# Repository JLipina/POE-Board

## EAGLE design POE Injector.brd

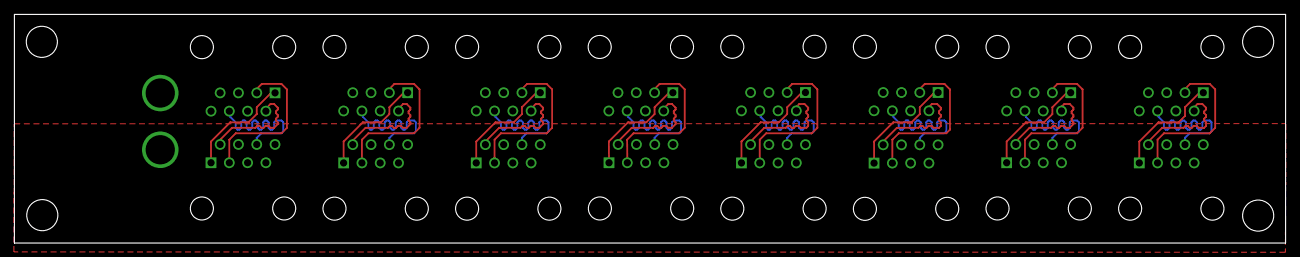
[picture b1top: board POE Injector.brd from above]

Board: 2 copper layers, 176.5 x 31.8 mm, 17 parts (0 on the bottom side), 34 nets.

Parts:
RJ45_ETH_1, RJ45_ETH_2, RJ45_ETH_3, RJ45_ETH_4, RJ45_ETH_5, RJ45_ETH_6, RJ45_ETH_7, RJ45_ETH_8, RJ45_POE_1, RJ45_POE_2, RJ45_POE_3, RJ45_POE_4, RJ45_POE_5, RJ45_POE_6, RJ45_POE_7, RJ45_POE_8: RJ45FCI-54602-908LF; FCI-54602-908LF
U$17: APP_2POS_CONFIG12V_HORIZ; APP45_12V_HORIZ_CONFIG

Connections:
+12V: RJ45_POE_1.4, RJ45_POE_1.5, RJ45_POE_2.4, RJ45_POE_2.5, RJ45_POE_3.4, RJ45_POE_3.5, RJ45_POE_4.4, RJ45_POE_4.5, RJ45_POE_5.4, RJ45_POE_5.5, RJ45_POE_6.4, RJ45_POE_6.5, RJ45_POE_7.4, RJ45_POE_7.5, RJ45_POE_8.4, RJ45_POE_8.5, U$17.12V
GND: RJ45_ETH_1.7, RJ45_ETH_1.8, RJ45_ETH_2.7, RJ45_ETH_2.8, RJ45_ETH_3.7, RJ45_ETH_3.8, RJ45_ETH_4.7, RJ45_ETH_4.8, RJ45_ETH_5.7, RJ45_ETH_5.8, RJ45_ETH_6.7, RJ45_ETH_6.8, RJ45_ETH_7.7, RJ45_ETH_7.8, RJ45_ETH_8.7, RJ45_ETH_8.8, RJ45_POE_1.7, RJ45_POE_1.8, RJ45_POE_2.7, RJ45_POE_2.8, RJ45_POE_3.7, RJ45_POE_3.8, RJ45_POE_4.7, RJ45_POE_4.8, RJ45_POE_5.7, RJ45_POE_5.8, RJ45_POE_6.7, RJ45_POE_6.8, RJ45_POE_7.7, RJ45_POE_7.8, RJ45_POE_8.7, RJ45_POE_8.8, U$17.GND
RX_N_1: RJ45_ETH_1.6, RJ45_POE_1.6
RX_N_2: RJ45_ETH_2.6, RJ45_POE_2.6
RX_N_3: RJ45_ETH_3.6, RJ45_POE_3.6
RX_N_4: RJ45_ETH_4.6, RJ45_POE_4.6
RX_N_5: RJ45_ETH_5.6, RJ45_POE_5.6
RX_N_6: RJ45_ETH_6.6, RJ45_POE_6.6
RX_N_7: RJ45_ETH_7.6, RJ45_POE_7.6
RX_N_8: RJ45_ETH_8.6, RJ45_POE_8.6
RX_P_1: RJ45_ETH_1.3, RJ45_POE_1.3
RX_P_2: RJ45_ETH_2.3, RJ45_POE_2.3
RX_P_3: RJ45_ETH_3.3, RJ45_POE_3.3
RX_P_4: RJ45_ETH_4.3, RJ45_POE_4.3
RX_P_5: RJ45_ETH_5.3, RJ45_POE_5.3
RX_P_6: RJ45_ETH_6.3, RJ45_POE_6.3
RX_P_7: RJ45_ETH_7.3, RJ45_POE_7.3
RX_P_8: RJ45_ETH_8.3, RJ45_POE_8.3
TX_N_1: RJ45_ETH_1.2, RJ45_POE_1.2
TX_N_2: RJ45_ETH_2.2, RJ45_POE_2.2
TX_N_3: RJ45_ETH_3.2, RJ45_POE_3.2
TX_N_4: RJ45_ETH_4.2, RJ45_POE_4.2
TX_N_5: RJ45_ETH_5.2, RJ45_POE_5.2
TX_N_6: RJ45_ETH_6.2, RJ45_POE_6.2
TX_N_7: RJ45_ETH_7.2, RJ45_POE_7.2
TX_N_8: RJ45_ETH_8.2, RJ45_POE_8.2
TX_P_1: RJ45_ETH_1.1, RJ45_POE_1.1
TX_P_2: RJ45_ETH_2.1, RJ45_POE_2.1
TX_P_3: RJ45_ETH_3.1, RJ45_POE_3.1
TX_P_4: RJ45_ETH_4.1, RJ45_POE_4.1
TX_P_5: RJ45_ETH_5.1, RJ45_POE_5.1
TX_P_6: RJ45_ETH_6.1, RJ45_POE_6.1
TX_P_7: RJ45_ETH_7.1, RJ45_POE_7.1
TX_P_8: RJ45_ETH_8.1, RJ45_POE_8.1

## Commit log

2016-01-24 rerouted data, added new connector, pre-desync
2016-01-25 copy/pasted brd layout - resynced
2016-01-25 need to swap remaining rj45's
    new rj45's: MRDT-2015-General>RJ45>FCI...
    be sure to re adjust origins and routing
2016-01-25 Replaced rj45's and fixed routing
    New rj45's are a more specific package so I was able to move them closer
    together and shorten the board. All signal traces are equal in length.
